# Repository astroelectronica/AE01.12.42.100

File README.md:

# AE01.12.42.100
- LTC4060
- NiCd/NiMH 1-4 cell battery charger

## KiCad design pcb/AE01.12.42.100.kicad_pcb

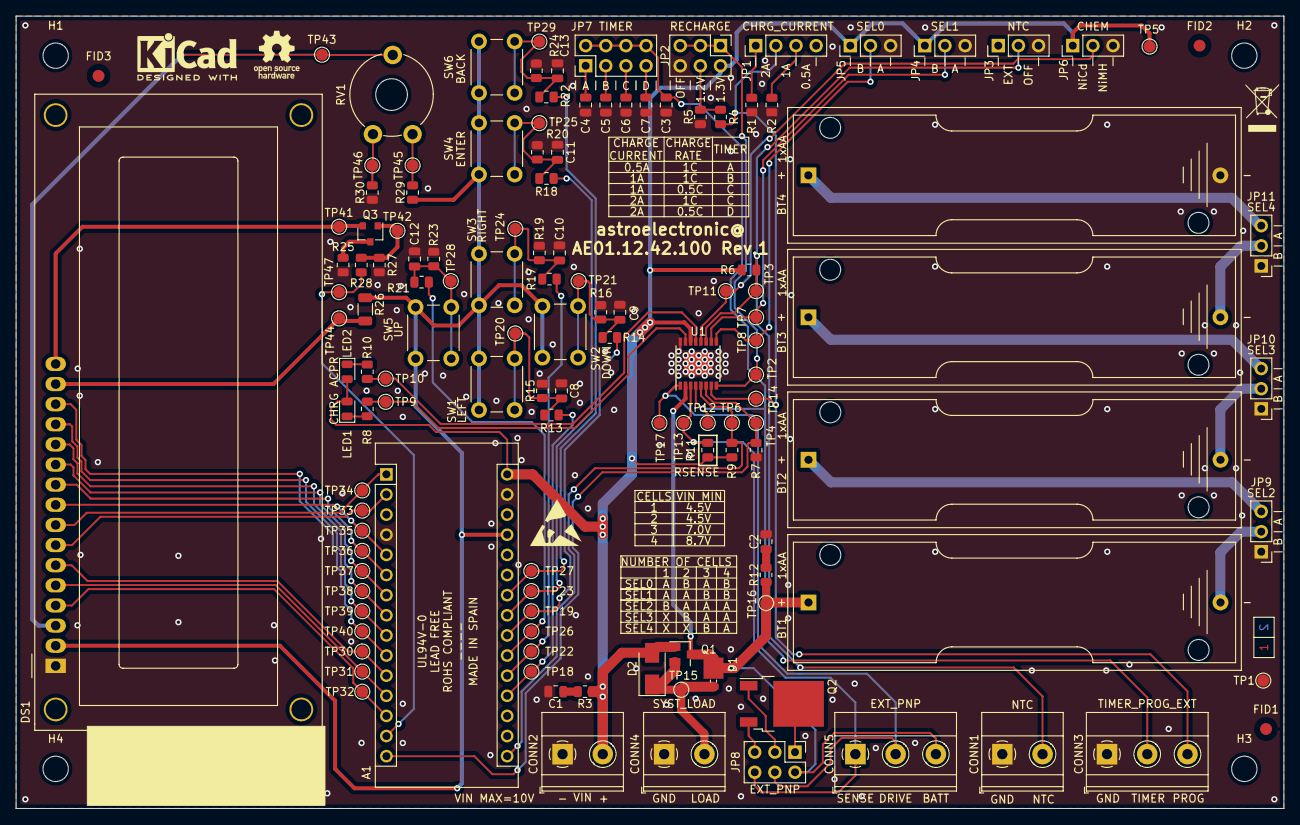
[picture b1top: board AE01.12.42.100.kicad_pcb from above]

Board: 2 copper layers, 160.0 x 100.0 mm, 138 parts (0 on the bottom side), 69 nets.

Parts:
A1: Arduino_Nano_v2.x; Arduino_Nano
BT1: CELL1; BatteryHolder_Keystone_2460_1xAA
BT2: CELL2; BatteryHolder_Keystone_2460_1xAA
BT3: CELL3; BatteryHolder_Keystone_2460_1xAA
BT4: CELL4; BatteryHolder_Keystone_2460_1xAA
C1: 1uF; C_0805_2012Metric
C2: 10uF; C_0805_2012Metric
C3: 220pF; C_0805_2012Metric
C4: 150pF; C_0805_2012Metric
C5: 470pF; C_0805_2012Metric
C6: 1200pF; C_0805_2012Metric
C7: 2700pF; C_0805_2012Metric
C8, C9, C10, C11, C12, C13: 10nF; C_0805_2012Metric
CONN1: NTC; TerminalBlock_Phoenix_MKDS-1,5-2-5.08_1x02_P5.08mm_Horizont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
CONN2: VIN; TerminalBlock_Phoenix_MKDS-1,5-2-5.08_1x02_P5.08mm_Horizont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
CONN3: TIMER_PROG_EXT; TerminalBlock_Phoenix_MKDS-1,5-3-5.08_1x03_P5.08mm_Horizont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
CONN4: SYST_LOAD; TerminalBlock_Phoenix_MKDS-1,5-2-5.08_1x02_P5.08mm_Horizont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
CONN5: EXT_PNP; TerminalBlock_Phoenix_MKDS-1,5-3-5.08_1x03_P5.08mm_Horizont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
D1: MBRM120LT3; D_Powermite_KA
D2: B220A; D_SMA
DS1: WC1602A
FID1, FID2, FID3: Fiducial; Fiducial_1.5mm_Mask3mm
H1, H2, H3, H4: M3_DIN965; MountingHole_3.2mm_M3_DIN965
JP1: CHRG_CURRENT; PinHeader_1x04_P2.54mm_Vertical
JP2: RECHARGE; PinHeader_2x03_P2.54mm_Vertical
JP3: NTC; PinHeader_1x03_P2.54mm_Vertical
JP4: SEL1; PinHeader_1x03_P2.54mm_Vertical
JP5: SEL0; PinHeader_1x03_P2.54mm_Vertical
JP6: CHEM; PinHeader_1x03_P2.54mm_Vertical
JP7: TIMER; PinHeader_2x04_P2.54mm_Vertical
JP8: EXT_PNP; PinHeader_2x03_P2.54mm_Vertical
JP9: SEL2; PinHeader_1x03_P2.54mm_Vertical
JP10: SEL3; PinHeader_1x03_P2.54mm_Vertical
JP11: SEL4; PinHeader_1x03_P2.54mm_Vertical
LED1: CHRG; LED_0805_2012Metric
LED2: ACPR; LED_0805_2012Metric
LOGO1: KiCad_logo; KiCad-Logo2_5mm_SilkScreen
LOGO2: Logo_Open_Hardware_Small; OSHW-Logo_5.7x6mm_SilkScreen
LOGO3: WEEE_logo; WEEE-Logo_4.2x6mm_SilkScreen
Q1: FDN306P; SuperSOT-3
Q2: MJD210T4G; TO-252-2
Q3: BC817-25; SOT-23
R1: 931R; R_0805_2012Metric
R2: 2.8K; R_0805_2012Metric
R3, R12: 1R; R_0805_2012Metric
R4: 576R; R_0805_2012Metric
R5: 2.21K; R_0805_2012Metric
R6: 4.42K; R_0805_2012Metric
R7: 68K; R_0805_2012Metric
R8, R10: 330R; R_0805_2012Metric
R9: 390K; R_0805_2012Metric
R11: RSENSE; R_0805_2012Metric
R13, R14, R17, R18, R21, R22, R28: 100R; R_0805_2012Metric
R15, R16, R19, R20, R23, R24, R27: 10K; R_0805_2012Metric
R25, R29, R30: 1K; R_0805_2012Metric
R26: 33R; R_1206_3216Metric
RV1: 10K; Potentiometer_Piher_PT-10-V10_Vertical_Hole
SW1: LEFT; SW_PUSH_6mm
SW2: DOWN; SW_PUSH_6mm
SW3: RIGHT; SW_PUSH_6mm
SW4: ENTER; SW_PUSH_6mm
SW5: UP; SW_PUSH_6mm
SW6: BACK; SW_PUSH_6mm
SYM1: SYM_ESD_Small; ESD-Logo_6.6x6mm_SilkScreen
TP1: GND; TestPoint_Pad_D1.5mm
TP2: ARCT; TestPoint_Pad_D1.5mm
TP3: NTC; TestPoint_Pad_D1.5mm
TP4: PAUSE; TestPoint_Pad_D1.5mm
TP5: VIN; TestPoint_Pad_D1.5mm
TP6: SHDN; TestPoint_Pad_D1.5mm
TP7: SEL1; TestPoint_Pad_D1.5mm
TP8: SEL0; TestPoint_Pad_D1.5mm
TP9: CHRG; TestPoint_Pad_D1.5mm
TP10: ACPR; TestPoint_Pad_D1.5mm
TP11: CHEM; TestPoint_Pad_D1.5mm
TP12: TIMER; TestPoint_Pad_D1.5mm
TP13: SENSE; TestPoint_Pad_D1.5mm
TP14: PROG; TestPoint_Pad_D1.5mm
TP15: SYST_LOAD; TestPoint_Pad_D1.5mm
TP16: BATT; TestPoint_Pad_D1.5mm
TP17: DRIVE; TestPoint_Pad_D1.5mm
TP18: LEFT; TestPoint_Pad_D1.5mm
TP19: DOWN; TestPoint_Pad_D1.5mm
TP20: LEFT_SW; TestPoint_Pad_D1.5mm
TP21: DOWN_SW; TestPoint_Pad_D1.5mm
TP22: RIGHT; TestPoint_Pad_D1.5mm
TP23: ENTER; TestPoint_Pad_D1.5mm
TP24: RIGHT_SW; TestPoint_Pad_D1.5mm
TP25: ENTER_SW; TestPoint_Pad_D1.5mm
TP26: UP; TestPoint_Pad_D1.5mm
TP27: BACK; TestPoint_Pad_D1.5mm
TP28: UP_SW; TestPoint_Pad_D1.5mm
TP29: BACK_SW; TestPoint_Pad_D1.5mm
TP30: LCD_EN; TestPoint_Pad_D1.5mm
TP31: LCD_RW; TestPoint_Pad_D1.5mm
TP32: LCD_RS; TestPoint_Pad_D1.5mm
TP33: LCD_D0; TestPoint_Pad_D1.5mm
TP34: LCD_D1; TestPoint_Pad_D1.5mm
TP35: LCD_D2; TestPoint_Pad_D1.5mm
TP36: LCD_D3; TestPoint_Pad_D1.5mm
TP37: LCD_D4; TestPoint_Pad_D1.5mm
TP38: LCD_D5; TestPoint_Pad_D1.5mm
TP39: LCD_D6; TestPoint_Pad_D1.5mm
TP40: LCD_D7; TestPoint_Pad_D1.5mm
TP41: LCD_BL_K; TestPoint_Pad_D1.5mm
TP42: LCD_BL_CTRL; TestPoint_Pad_D1.5mm
TP43: CONT; TestPoint_Pad_D1.5mm
TP44: LCD_BL_A; TestPoint_Pad_D1.5mm
TP45: CONT_H; TestPoint_Pad_D1.5mm
TP46: CONT_L; TestPoint_Pad_D1.5mm
TP47: LCD_BL; TestPoint_Pad_D1.5mm
U1: LTC4060EFE; TSSOP-16-1EP_4.4x5mm_P0.65mm

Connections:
+5V: A1.27, DS1.2, R26.1, R29.1, SW1.1, SW2.1, SW3.1, SW4.1, SW5.1, SW6.1
/PAUSE: A1.15, R7.1, TP4.1, U1.6
/charger/ARCT: JP2.1, JP2.3, JP2.5, TP2.1, U1.8
/charger/BATT: BT1.1, CONN5.3, D1.2, JP8.2, Q1.3, R12.1, TP16.1, U1.2
/charger/CHEM: JP6.2, TP11.1, U1.12
/charger/DRIVE: CONN5.2, JP8.4, TP17.1, U1.1
/charger/NTC: CONN1.2, JP3.2, R6.2, TP3.1, U1.11
/charger/PNP_B: JP8.3, Q2.1
/charger/PNP_C: JP8.1, Q2.2
/charger/PNP_E: JP8.5, Q2.3
/charger/PROG: CONN3.3, JP1.2, R4.1, TP14.1, U1.7
/charger/SEL0: JP5.2, TP8.1, U1.9
/charger/SEL1: JP4.2, TP7.1, U1.10
/charger/SENSE: CONN5.1, JP8.6, R11.2, TP13.1, U1.3
/charger/SYST_LOAD: CONN4.2, D1.1, D2.1, Q1.2, TP15.1
/charger/TIMER: C3.1, CONN3.2, JP7.2, JP7.4, JP7.6, JP7.8, TP12.1, U1.4
/charger/~ACPR: R10.2, TP10.1, U1.13
/charger/~CHRG: R8.2, TP9.1, U1.15
/control/BACK: A1.24, R22.2, TP27.1
/control/CONTRAST: DS1.3, RV1.2, TP43.1
/control/DOWN: A1.22, R14.2, TP19.1
/control/ENTER: A1.23, R18.2, TP23.1
/control/LCD_BL: A1.14, R28.1, TP47.1
/control/LCD_BL_A: DS1.15, R26.2, TP44.1
/control/LCD_BL_CTRL: Q3.1, R27.1, R28.2, TP42.1
/control/LCD_BL_K: DS1.16, Q3.2, TP41.1
/control/LCD_D0: A1.2, DS1.7, TP33.1
/control/LCD_D1: A1.1, DS1.8, TP34.1
/control/LCD_D2: A1.5, DS1.9, TP35.1
/control/LCD_D3: A1.6, DS1.10, TP36.1
/control/LCD_D4: A1.7, DS1.11, TP37.1
/control/LCD_D5: A1.8, DS1.12, TP38.1
/control/LCD_D6: A1.9, DS1.13, TP39.1
/control/LCD_D7: A1.10, DS1.14, TP40.1
/control/LCD_EN: A1.11, DS1.6, TP30.1
/control/LCD_RS: A1.13, DS1.4, TP32.1
/control/LCD_RW: A1.12, DS1.5, TP31.1
/control/LEFT: A1.19, R13.2, TP18.1
/control/RIGHT: A1.20, R17.2, TP22.1
/control/UP: A1.21, R21.2, TP26.1
/~SHDN: A1.16, R9.2, TP6.1, U1.5
GND: A1.4, A1.29, BT4.2, C1.2, C2.2, C3.2, C4.1, C5.1, C6.1, C7.1, C8.2, C9.2, C10.2, C11.2, C12.2, C13.2, CONN1.1, CONN2.1, CONN3.1, CONN4.1, DS1.1, JP2.6, JP3.3, JP4.3, JP5.3, JP6.3, JP9.1, JP10.1, JP11.1, R1.1, R2.1, R5.2, R7.2, R15.2, R16.2, R19.2, R20.2, R23.2, R24.2, R25.2, R27.2, R30.2, TP1.1, U1.16, U1.17
unnamed: BT1.2, JP9.2
unnamed: BT2.1, JP9.3
unnamed: BT2.2, JP10.2
unnamed: BT3.1, JP10.3
unnamed: BT3.2, JP11.2
unnamed: BT4.1, JP11.3
unnamed: C1.1, R3.2
unnamed: C2.1, R12.2
unnamed: C4.2, JP7.1
unnamed: C5.2, JP7.3
unnamed: C6.2, JP7.5
unnamed: C7.2, JP7.7
unnamed: C8.1, R13.1, R15.1, SW1.2, TP20.1
unnamed: C9.1, R14.1, R16.1, SW2.2, TP21.1
unnamed: C10.1, R17.1, R19.1, SW3.2, TP24.1
unnamed: C11.1, R18.1, R20.1, SW4.2, TP25.1
unnamed: C12.1, R21.1, R23.1, SW5.2, TP28.1
unnamed: C13.1, R22.1, R24.1, SW6.2, TP29.1
unnamed: JP1.1, R1.2
unnamed: JP1.3, R2.2
unnamed: JP2.4, R4.2, R5.1
unnamed: LED1.1, R8.1
unnamed: LED2.1, R10.1
unnamed: Q3.3, R25.1
unnamed: R29.2, RV1.1, TP45.1
unnamed: R30.1, RV1.3, TP46.1
VCC: A1.30, CONN2.2, D2.2, JP2.2, JP4.1, JP5.1, JP6.1, LED1.2, LED2.2, Q1.1, R3.1, R6.1, R9.1, R11.1, TP5.1, U1.14

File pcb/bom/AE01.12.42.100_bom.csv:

Source:,/home/astroelectronica/kicad/projects/AE01.12.42.100/pcb/AE01.12.42.100.sch,,,,
Date:,sáb 02 oct 2021 00:14:59 CEST,,,,
Tool:,Eeschema 5.1.10-88a1d61d58~88~ubuntu16.04.1,,,,
Component Count:,91,,,,
Ref,Value,Footprint,Datasheet,Manufacturer,Vendor
A1,Arduino_Nano_v2.x,Module:Arduino_Nano,~,,
BT1,CELL1,Battery:BatteryHolder_Keystone_2460_1xAA,~,,
BT2,CELL2,Battery:BatteryHolder_Keystone_2460_1xAA,~,,
BT3,CELL3,Battery:BatteryHolder_Keystone_2460_1xAA,~,,
BT4,CELL4,Battery:BatteryHolder_Keystone_2460_1xAA,~,,
C1,1uF,Capacitor_SMD:C_0805_2012Metric,~,,
C2,10uF,Capacitor_SMD:C_0805_2012Metric,~,,
C3,220pF,Capacitor_SMD:C_0805_2012Metric,~,,
C4,150pF,Capacitor_SMD:C_0805_2012Metric,~,,
C5,470pF,Capacitor_SMD:C_0805_2012Metric,~,,
C6,1200pF,Capacitor_SMD:C_0805_2012Metric,~,,
C7,2700pF,Capacitor_SMD:C_0805_2012Metric,~,,
C8,10nF,Capacitor_SMD:C_0805_2012Metric,~,,
C9,10nF,Capacitor_SMD:C_0805_2012Metric,~,,
C10,10nF,Capacitor_SMD:C_0805_2012Metric,~,,
C11,10nF,Capacitor_SMD:C_0805_2012Metric,~,,
C12,10nF,Capacitor_SMD:C_0805_2012Metric,~,,
C13,10nF,Capacitor_SMD:C_0805_2012Metric,~,,
CONN1,NTC,"TerminalBlock_Phoenix:TerminalBlock_Phoenix_MKDS-1,5-2-5.08_1x02_P5.08mm_Horizontal",~,,
CONN2,VIN,"TerminalBlock_Phoenix:TerminalBlock_Phoenix_MKDS-1,5-2-5.08_1x02_P5.08mm_Horizontal",~,,
CONN3,TIMER_PROG_EXT,"TerminalBlock_Phoenix:TerminalBlock_Phoenix_MKDS-1,5-3-5.08_1x03_P5.08mm_Horizontal",~,,
CONN4,SYST_LOAD,"TerminalBlock_Phoenix:TerminalBlock_Phoenix_MKDS-1,5-2-5.08_1x02_P5.08mm_Horizontal",~,,
CONN5,EXT_PNP,"TerminalBlock_Phoenix:TerminalBlock_Phoenix_MKDS-1,5-3-5.08_1x03_P5.08mm_Horizontal",~,,
D1,MBRM120LT3,Diode_SMD:D_Powermite_KA,~,,
D2,B220A,Diode_SMD:D_SMA,~,,
DS1,WC1602A,Display:WC1602A,~,,
FID1,Fiducial,Fiducial:Fiducial_1.5mm_Mask3mm,~,,
FID2,Fiducial,Fiducial:Fiducial_1.5mm_Mask3mm,~,,
FID3,Fiducial,Fiducial:Fiducial_1.5mm_Mask3mm,~,,
H1,M3_DIN965,MountingHole:MountingHole_3.2mm_M3_DIN965,~,,
H2,M3_DIN965,MountingHole:MountingHole_3.2mm_M3_DIN965,~,,
H3,M3_DIN965,MountingHole:MountingHole_3.2mm_M3_DIN965,~,,
H4,M3_DIN965,MountingHole:MountingHole_3.2mm_M3_DIN965,~,,
JP1,CHRG_CURRENT,Connector_PinHeader_2.54mm:PinHeader_1x04_P2.54mm_Vertical,~,,
JP2,RECHARGE,Connector_PinHeader_2.54mm:PinHeader_2x03_P2.54mm_Vertical,~,,
JP3,NTC,Connector_PinHeader_2.54mm:PinHeader_1x03_P2.54mm_Vertical,~,,
JP4,SEL1,Connector_PinHeader_2.54mm:PinHeader_1x03_P2.54mm_Vertical,~,,
JP5,SEL0,Connector_PinHeader_2.54mm:PinHeader_1x03_P2.54mm_Vertical,~,,
JP6,CHEM,Connector_PinHeader_2.54mm:PinHeader_1x03_P2.54mm_Vertical,~,,
JP7,TIMER,Connector_PinHeader_2.54mm:PinHeader_2x04_P2.54mm_Vertical,~,,
JP8,EXT_PNP,Connector_PinHeader_2.54mm:PinHeader_2x03_P2.54mm_Vertical,~,,
JP9,SEL2,Connector_PinHeader_2.54mm:PinHeader_1x03_P2.54mm_Vertical,~,,
JP10,SEL3,Connector_PinHeader_2.54mm:PinHeader_1x03_P2.54mm_Vertical,~,,
JP11,SEL4,Connector_PinHeader_2.54mm:PinHeader_1x03_P2.54mm_Vertical,~,,
LED1,CHRG,LED_SMD:LED_0805_2012Metric,~,,
LED2,ACPR,LED_SMD:LED_0805_2012Metric,~,,
LOGO1,KiCad_logo,Symbol:KiCad-Logo2_5mm_SilkScreen,~,,
LOGO2,Logo_Open_Hardware_Small,Symbol:OSHW-Logo_5.7x6mm_SilkScreen,~,,
LOGO3,WEEE_logo,Symbol:WEEE-Logo_4.2x6mm_SilkScreen,~,,
Q1,FDN306P,Package_TO_SOT_SMD:SuperSOT-3,~,,
Q2,MJD210T4G,Package_TO_SOT_SMD:TO-252-2,~,,
Q3,BC817-25,Package_TO_SOT_SMD:SOT-23,~,,
R1,931R,Resistor_SMD:R_0805_2012Metric,~,,
R2,2.8K,Resistor_SMD:R_0805_2012Metric,~,,
R3,1R,Resistor_SMD:R_0805_2012Metric,~,,
R4,576R,Resistor_SMD:R_0805_2012Metric,~,,
R5,2.21K,Resistor_SMD:R_0805_2012Metric,~,,
R6,4.42K,Resistor_SMD:R_0805_2012Metric,~,,
R7,68K,Resistor_SMD:R_0805_2012Metric,~,,
R8,330R,Resistor_SMD:R_0805_2012Metric,~,,
R9,390K,Resistor_SMD:R_0805_2012Metric,~,,
R10,330R,Resistor_SMD:R_0805_2012Metric,~,,
R11,RSENSE,Resistor_SMD:R_0805_2012Metric,~,,
R12,1R,Resistor_SMD:R_0805_2012Metric,~,,
R13,100R,Resistor_SMD:R_0805_2012Metric,~,,
R14,100R,Resistor_SMD:R_0805_2012Metric,~,,
R15,10K,Resistor_SMD:R_0805_2012Metric,~,,
R16,10K,Resistor_SMD:R_0805_2012Metric,~,,
R17,100R,Resistor_SMD:R_0805_2012Metric,~,,
R18,100R,Resistor_SMD:R_0805_2012Metric,~,,
R19,10K,Resistor_SMD:R_0805_2012Metric,~,,
R20,10K,Resistor_SMD:R_0805_2012Metric,~,,
R21,100R,Resistor_SMD:R_0805_2012Metric,~,,
R22,100R,Resistor_SMD:R_0805_2012Metric,~,,
R23,10K,Resistor_SMD:R_0805_2012Metric,~,,
R24,10K,Resistor_SMD:R_0805_2012Metric,~,,
R25,1K,Resistor_SMD:R_0805_2012Metric,~,,
R26,33R,Resistor_SMD:R_1206_3216Metric,~,,
R27,10K,Resistor_SMD:R_0805_2012Metric,~,,
R28,100R,Resistor_SMD:R_0805_2012Metric,~,,
R29,1K,Resistor_SMD:R_0805_2012Metric,~,,
R30,1K,Resistor_SMD:R_0805_2012Metric,~,,
RV1,10K,Potentiometer_THT:Potentiometer_Piher_PT-10-V10_Vertical_Hole,~,,
SW1,LEFT,Button_Switch_THT:SW_PUSH_6mm,~,,
SW2,DOWN,Button_Switch_THT:SW_PUSH_6mm,~,,
SW3,RIGHT,Button_Switch_THT:SW_PUSH_6mm,~,,
SW4,ENTER,Button_Switch_THT:SW_PUSH_6mm,~,,
SW5,UP,Button_Switch_THT:SW_PUSH_6mm,~,,
SW6,BACK,Button_Switch_THT:SW_PUSH_6mm,~,,
SYM1,SYM_ESD_Small,Symbol:ESD-Logo_6.6x6mm_SilkScreen,~,,
U1,LTC4060EFE,Package_SO:TSSOP-16-1EP_4.4x5mm_P0.65mm,~,,
